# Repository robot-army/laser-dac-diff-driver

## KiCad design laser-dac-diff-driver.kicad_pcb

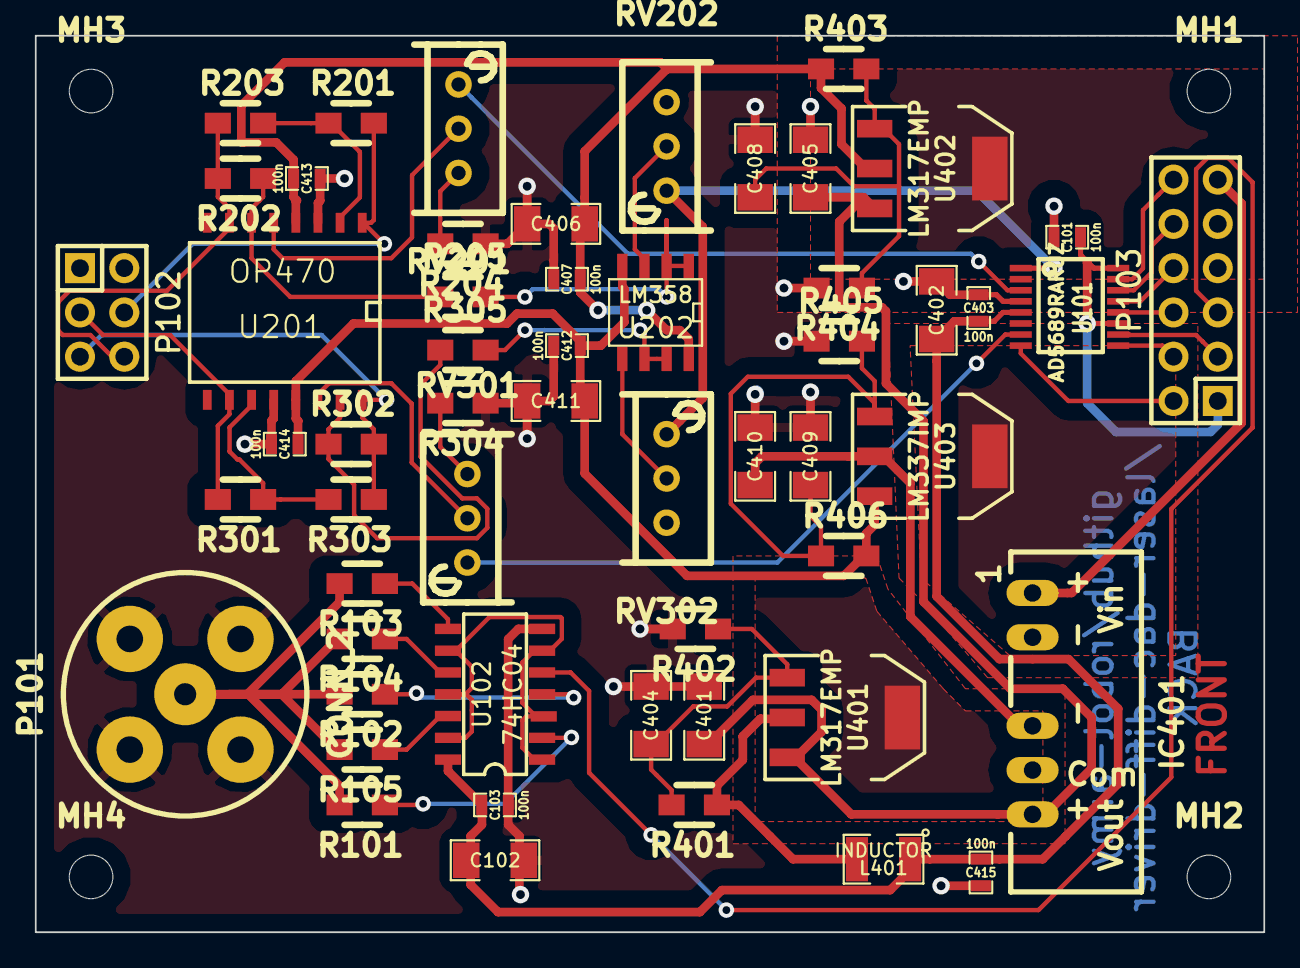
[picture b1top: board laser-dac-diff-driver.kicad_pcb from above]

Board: 2 copper layers, 70.5 x 51.4 mm, 59 parts (0 on the bottom side), 46 nets.

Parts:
C101, C103, C403, C407, C412, C413, C414, C415: 100n; SM0603_Capa
C102, C401, C402, C405, C406, C410, C411: 1u; SM1206
C404, C408, C409: 10u; SM1206
IC401: DCDC-CONV_TRACO_TMH-XXXX_Dual_REVA_27MAR2011; DCDC-Conv_TRACO_TMH-xxxx_Dual_RevA_27Mar2011
L401: INDUCTOR; SM1210
MH1, MH2, MH3, MH4: MountingHole_2-5mm_RevA_Date21Jun2010; MountingHole_2-5mm
P101: CONN_2; bnc-ci
P102: CONN_3X2; Pin_Header_Straight_2x03
P103: CONN_6X2; Pin_Header_Straight_2x06
R101, R102, R103, R104, R105: R; Resistor_SMD0805_HandSoldering
R201, R203, R205, R301, R303, R305: 10k; Resistor_SMD0805_HandSoldering
R202, R302: 47k; Resistor_SMD0805_HandSoldering
R204, R304: 8k2; Resistor_SMD0805_HandSoldering
R401, R403, R406: 240R; Resistor_SMD0805_HandSoldering
R402: 680R; Resistor_SMD0805_HandSoldering
R404, R405: 1k8; Resistor_SMD0805_HandSoldering
RV201, RV301: 1kPOT; Potentiometer_Bourns_3296W_3-8Zoll_Inline_ScrewUp
RV202, RV302: 10kPOT; Potentiometer_Bourns_3296W_3-8Zoll_Inline_ScrewUp
U101: AD5689RARUZ; TSSOP16
U102: 74HC04; SOIC-14_Narrow
U201: OP470; SO16W
U202: LM358; SO8E
U401, U402: LM317EMP; SOT223
U403: LM337IMP; SOT223

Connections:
+3.3VDAC: C101.1, P103.1, U101.11, U101.16
+5VD: C102.1, C103.1, C402.1, C403.1, C415.1, L401.1, U101.5, U102.14
-VAA: C411.2, C412.2, C414.2, R406.2, U201.13, U202.4, U403.3
/GAIN: P103.3, U101.10
/MOD_IN: P103.5, U102.5
/MOD_OUT: P101.1, R101.2, R102.2, R103.2, R104.2, R105.2
/SCLK: P103.6, U101.12
/SDIN: P103.10, U101.14
/SDO: P103.2, U101.8
/analog2/In1: RV301.1, U101.7
/analog2/Out1+: P102.5, R302.2, R303.1, U201.16
/analog2/Out1-: P102.3, R301.2, U201.10
/analog/+Vref: RV202.1, RV302.1, U101.1
/analog/In1: RV201.1, U101.3
/analog/Out1+: P102.6, R202.2, R203.1, U201.7
/analog/Out1-: P102.4, R201.2, U201.1
/powersupply/+Vin: IC401.1, P103.11
/powersupply/+Vout_unreg: C401.1, C405.1, IC401.6, U401.3, U402.3
/powersupply/-Vout_unreg: C410.2, IC401.4, U403.2, U403.4
/~LDAC: P103.4, U101.9
/~RESET: P103.12, U101.15
/~SYNC: P103.8, U101.13
AGND: C101.2, C102.2, C103.2, C401.2, C402.2, C403.2, C404.2, C405.2, C406.2, C407.2, C408.2, C409.1, C410.1, C411.1, C412.1, C413.2, C414.1, C415.2, IC401.2, IC401.5, P101.2, P102.1, P102.2, P103.7, P103.9, R204.1, R304.1, R402.2, R404.2, R405.1, RV202.3, RV302.3, U101.4, U102.7, U201.3, U201.12
unnamed: C404.1, R401.2, R402.1, U401.1
unnamed: C408.1, R403.2, R404.1, U402.1
unnamed: C409.2, R405.2, R406.1, U403.1
unnamed: L401.2, R401.1, U401.2, U401.4
unnamed: R101.1, U102.2
unnamed: R102.1, U102.4
unnamed: R103.1, U102.8
unnamed: R104.1, U102.10
unnamed: R105.1, U102.12
unnamed: R201.1, R203.2, U201.2
unnamed: R202.1, R205.1, U201.6
unnamed: R204.2, RV201.3
unnamed: R205.2, U202.1, U202.2
unnamed: R301.1, R303.2, U201.11
unnamed: R302.1, R305.1, U201.15
unnamed: R304.2, RV301.3
unnamed: R305.2, U202.6, U202.7
unnamed: RV201.2, U201.5
unnamed: RV202.2, U202.3
unnamed: RV301.2, U201.14
unnamed: RV302.2, U202.5
unnamed: U102.1, U102.3, U102.6, U102.9, U102.11, U102.13
VAA: C406.1, C407.1, C413.1, R403.1, U201.4, U202.8, U402.2, U402.4

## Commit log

2014-02-11 Adding schematic files and some custom libs
2014-02-11 Adding license
2014-02-11 Added more libraries and PCB layout starting point
2014-02-20 Fixed hidden pins and decoupling on 74HC04, sorted out component positions
2014-02-20 Fixed decoupling on 78HC04, sorted out component positions
2014-02-26 Moved that thing over there
2014-02-26 Revert "Moved that thing over there"
    This reverts commit 1365cc426dc2828d99ed98a10d059501ce40436a.
2014-02-27 Fixed component footprint for ADC chip (pitch was slightly wrong??) Changed over BNC to nice small footprint
2014-02-27 More component moves
2014-02-27 Power supply position changes
2014-02-28 Sorted out more component positions
2014-02-28 Added extra small decoupling for reference. Pin-swapped and fixed pin numbers on digital input.
2014-03-01 Started layout, final-ish positions
2014-03-01 Added net-names for unregulated DCDC outputs, more layout done
2014-03-03 Made SVG schematics, started layout (but it's ugly, need to re-visit positions)
2014-03-04 A few autorouter attempts and a new board layout (component positions). Removed voltage selector for MOD driver, 5V only now.
2014-03-05 Almost there with layout
2014-03-05 adding PDFs
2014-03-05 Richard: add 10K pot between LM358 and OP470
2014-03-06 SENT TO FAB - also added LC filter to power from 5V to dac, copper pours for Reg heatsinks and missing resistors
2014-03-06 Added PDFs
2014-03-12 Added bill of materials (shouldn't REALLY be any non-bom changes??)
